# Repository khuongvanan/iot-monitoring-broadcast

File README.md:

# IoT Monitoring & Broadcast

Hệ thống giám sát nhiệt độ, độ ẩm và báo lửa; nhận văn bản hoặc MP3 từ ThingsBoard để phát qua loa. ESP32-S3 xử lý cảm biến, truyền dữ liệu qua modem 4G và điều khiển âm thanh. Cảnh báo lửa được ưu tiên tại thiết bị.

## Sơ đồ hệ thống

```mermaid
flowchart TD
  UI[Dashboard ThingsBoard] <--> TB[ThingsBoard]
  TB <--> MODEM[Modem A7680C]
  MODEM <--> MCU[ESP32-S3]
  SENSOR[SHT31 và cảm biến lửa] --> MCU
  MCU --> DAC[PCM5102A]
  DAC --> AMP[TPA3118D2]
  AMP --> SPK[Loa]
```

## Phần cứng

| Khối | Thành phần | Thư mục |
|---|---|---|
| Điều khiển | ESP32-S3, nguồn và USB | hardware/esp32-controller |
| DAC | PCM5102A | hardware/audio-dac |
| Khuếch đại | TPA3118D2 | hardware/power-amplifier |
| Truyền thông | Modem A7680C qua UART | Module ngoài |
| Cảm biến | SHT31 và cảm biến lửa digital | Kết nối GPIO |

Tên file KiCad bên trong mỗi thư mục được giữ để bảo toàn liên kết project. Thư viện tùy chỉnh rời và model 3D chưa đầy đủ; cần bổ sung trước khi cập nhật linh kiện từ thư viện. Chạy ERC/DRC và tạo Gerber từ PCB trước khi gia công.

## Dùng nhanh

1. Copy `firmware/School_Node/secrets.example.h` thành `secrets.h` cùng thư mục; cấu hình riêng không đưa vào Git.
2. Mở `School_Node.ino` trong Arduino IDE. Cấu hình Arduino-ESP32 3.3.2, ArduinoJson 7.3.2 và flash/PSRAM theo module thực tế.
3. Import `thingsboard/dashboard.json`, chọn lại entity alias và thiết bị điều khiển.
4. Đọc [hướng dẫn sử dụng](docs/usage.md), đặc biệt phần giới hạn TLS, trước khi kết nối dịch vụ.

**Trạng thái TLS:** chỉ có cấu hình TLS cho TTS. HTTPS tới ThingsBoard hiện bị từ chối với mã `-12`; chưa hỗ trợ TLS ThingsBoard hoàn chỉnh. HTTP không bảo vệ token và nội dung trên đường truyền. Không dùng HTTP cho triển khai thực tế có dữ liệu hoặc thông tin xác thực cần bảo vệ.

## Cấu trúc

- `firmware/School_Node`: firmware Arduino và cấu hình mẫu.
- `hardware`: schematic, PCB, project và BOM có sẵn.
- `thingsboard`: một dashboard và mã nguồn widget.
- `tests`: kiểm thử upload, widget và giải mã MP3 trên máy tính.
- `docs/usage.md`: cấu hình, giao thức và xử lý lỗi.

Giới hạn ứng dụng: tối đa 128 KiB văn bản UTF-8, 2 MiB MP3 khi đủ PSRAM; mỗi chunk tối đa 1536 byte. Giới hạn thực tế phụ thuộc bộ nhớ khả dụng.

Xem [kết quả kiểm thử](tests/VALIDATION.md) và [lịch sử thay đổi](CHANGELOG.md). Quyền sử dụng được nêu trong LICENSE; thư viện bên thứ ba có điều khoản riêng trong THIRD_PARTY_NOTICES.txt.

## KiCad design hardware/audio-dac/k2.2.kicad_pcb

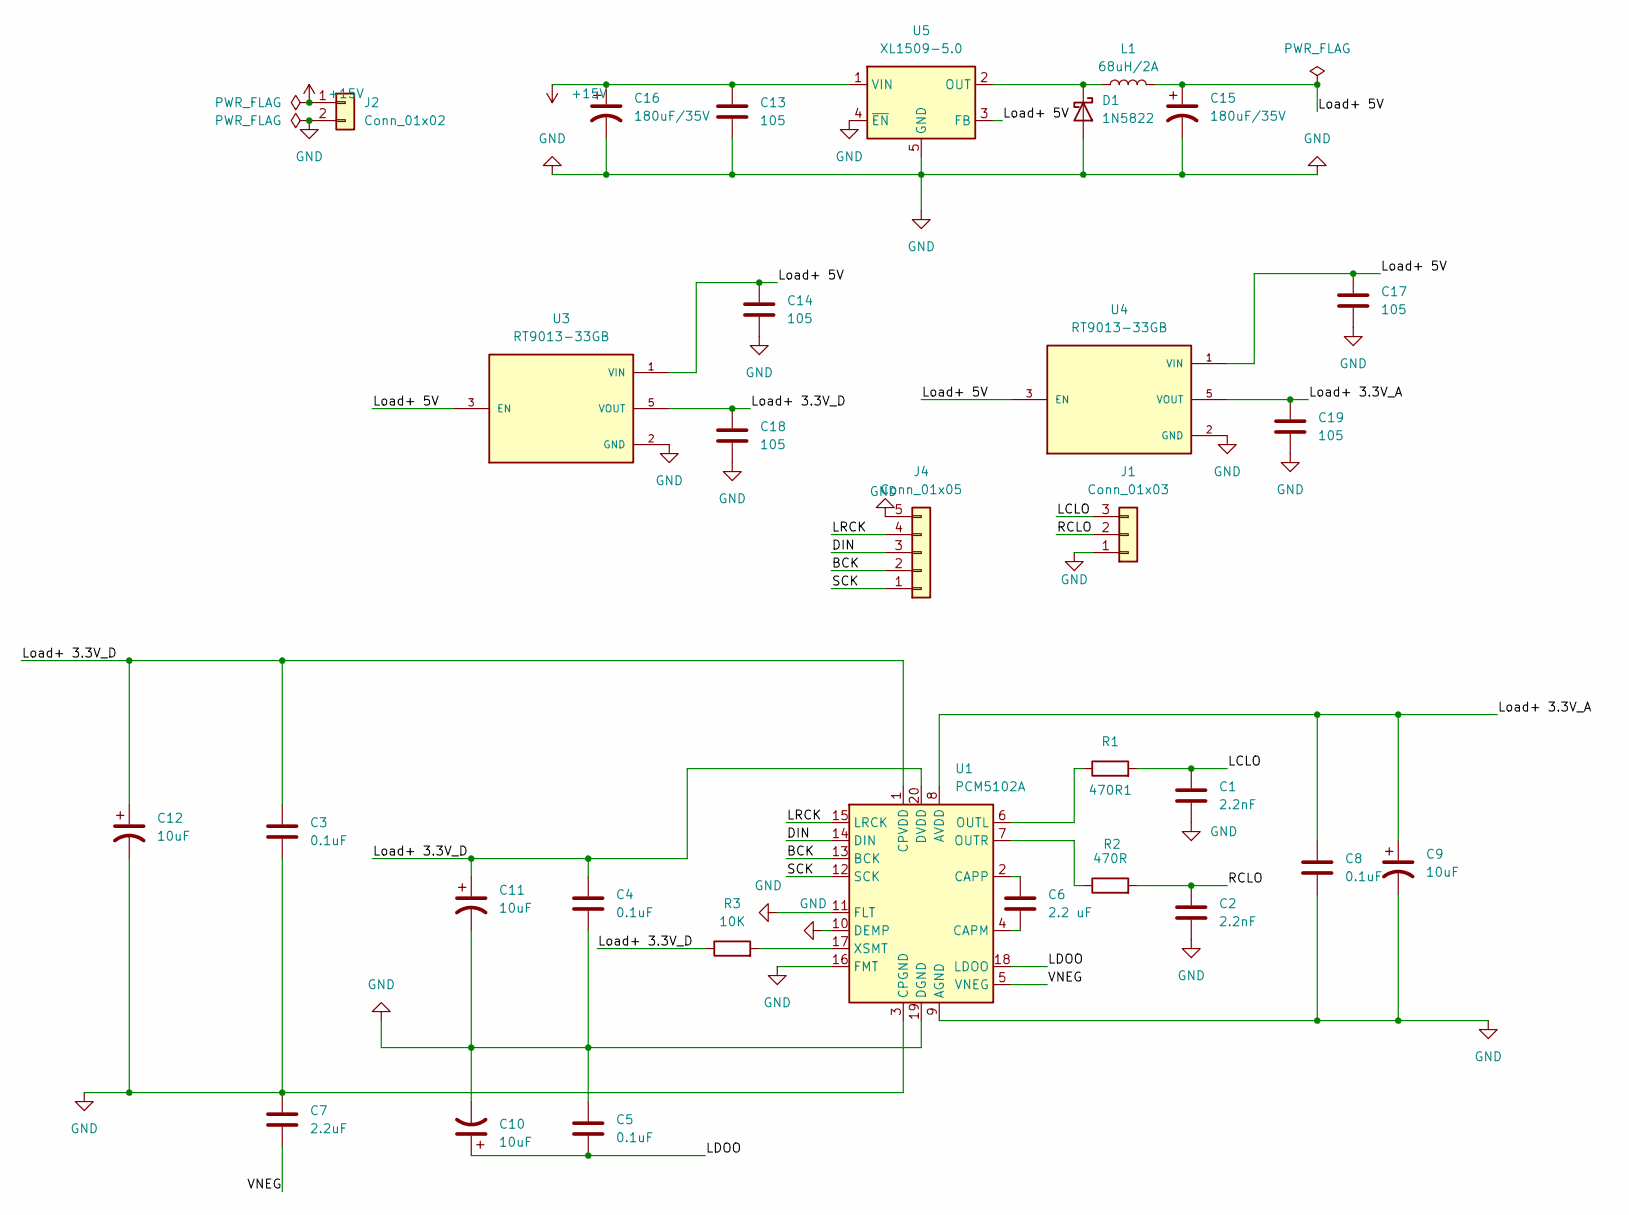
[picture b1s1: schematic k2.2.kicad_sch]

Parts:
470R1: R1; R_0805_2012Metric_Pad1.20x1.40mm_HandSolder
C1, C2: 2.2nF; C_0805_2012Metric_Pad1.18x1.45mm_HandSolder
C3, C4, C5, C8: 0.1uF; C_0805_2012Metric_Pad1.18x1.45mm_HandSolder
C6: 2.2 uF; C_0805_2012Metric_Pad1.18x1.45mm_HandSolder
C7: 2.2uF; C_0805_2012Metric_Pad1.18x1.45mm_HandSolder
C9, C10, C11, C12: 10uF; C_0805_2012Metric_Pad1.18x1.45mm_HandSolder
C13, C14, C17, C18, C19: 105; C_0805_2012Metric_Pad1.18x1.45mm_HandSolder
C15, C16: 180uF/35V; CP_Radial_D6.3mm_P2.50mm
D1: 1N5822; D_SMC_Handsoldering
J1: Conn_01x03; JST_EH_B3B-EH-A_1x03_P2.50mm_Vertical
J2: Conn_01x02; TerminalBlock_Phoenix_MKDS-1,5-2_1x02_P5.00mm_Horizontal
J4: Conn_01x05; JST_EH_B5B-EH-A_1x05_P2.50mm_Vertical
L1: 68uH/2A; L_Taiyo-Yuden_NR-80xx_HandSoldering
R2: 470R; R_0805_2012Metric_Pad1.20x1.40mm_HandSolder
R3: 10K; R_0805_2012Metric_Pad1.20x1.40mm_HandSolder
U1: PCM5102A; TSSOP-20_4.4x6.5mm_P0.65mm
U3, U4: RT9013-33GB; SOT94P279X129-5N; PARTREV Aprill 2011
U5: XL1509-5.0; SOIC-8_3.9x4.9mm_P1.27mm

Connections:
+15V: C13.1, C16.1, J2.1, U5.1 (VIN)
/BCK: J4.2, U1.13 (BCK); also elsewhere on the board
/DIN: J4.3, U1.14 (DIN); also elsewhere on the board
/LCLO: 470R1.2, C1.2, J1.3; also elsewhere on the board
/LDOO: C5.2, C10.1, U1.18 (LDOO)
/LRCK: J4.4, U1.15 (LRCK); also elsewhere on the board
/Load+ 3.3V_A: C8.1, C9.1, C19.1, U1.8 (AVDD), U4.5 (VOUT)
/Load+ 3.3V_D: C3.1, C4.1, C11.1, C12.1, C18.1, R3.1, U1.1 (CPVDD), U1.20 (DVDD), U3.5 (VOUT)
/Load+ 5V: C14.1, C15.1, C17.1, L1.2, U3.1 (VIN), U3.3 (EN), U4.1 (VIN), U4.3 (EN), U5.3 (FB)
/RCLO: C2.2, J1.2, R2.2
/SCK: J4.1, U1.12 (SCK); also elsewhere on the board
/VNEG: C7.1, U1.5 (VNEG)
GND: C1.1, C2.1, C3.2, C4.2, C5.1, C7.2, C8.2, C9.2, C10.2, C11.2, C12.2, C13.2, C14.2, C15.2, C16.2, C17.2, C18.2, C19.2, D1.2 (A), J1.1, J2.2, J4.5, U1.3 (CPGND), U1.9 (AGND), U1.10 (DEMP), U1.11 (FLT), U1.16 (FMT), U1.19 (DGND), U3.2 (GND), U4.2 (GND), U5.4 (~EN), U5.5 (GND), U5.6 (GND), U5.7 (GND), U5.8 (GND); also elsewhere on the board
unnamed: D1.1 (K), L1.1, U5.2 (OUT)
unnamed: C6.2, U1.4 (CAPM)
unnamed: C6.1, U1.2 (CAPP)
unnamed 16: 470R1.1, U1.6 (OUTL); also elsewhere on the board
unnamed: R2.1, U1.7 (OUTR)
unnamed: R3.2, U1.17 (XSMT)

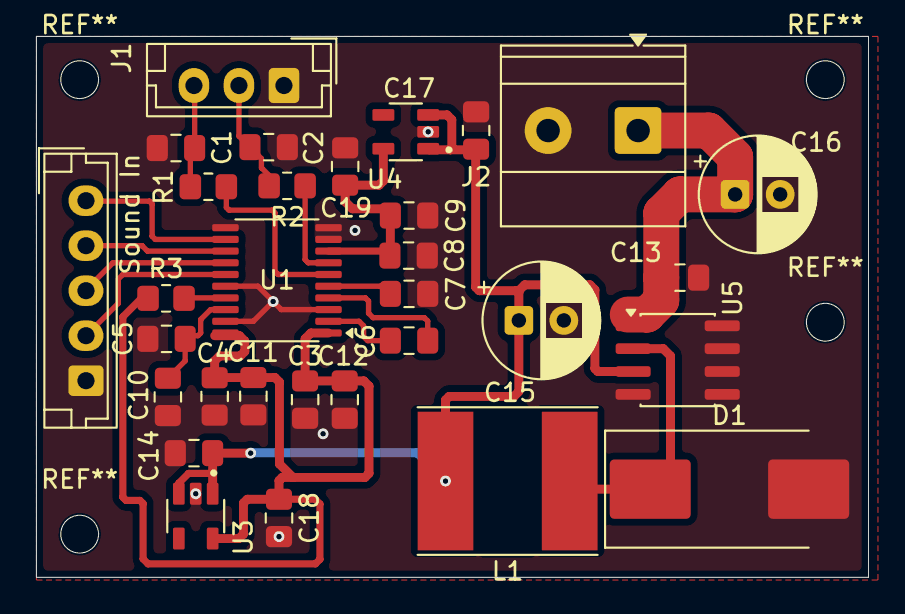
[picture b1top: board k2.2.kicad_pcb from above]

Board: 2 copper layers, 46.2 x 30.0 mm, 31 parts (0 on the bottom side), 19 nets.

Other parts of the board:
R1: R1; R_0805_2012Metric_Pad1.20x1.40mm_HandSolder
Sound In: Conn_01x05; JST_EH_B5B-EH-A_1x05_P2.50mm_Vertical

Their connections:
/BCK: Sound In.2; also elsewhere on the board
/DIN: Sound In.3; also elsewhere on the board
/LCLO: R1.2; also elsewhere on the board
/LRCK: Sound In.4; also elsewhere on the board
/SCK: Sound In.1; also elsewhere on the board
GND: Sound In.5; also elsewhere on the board
unnamed 16: R1.1; also elsewhere on the board

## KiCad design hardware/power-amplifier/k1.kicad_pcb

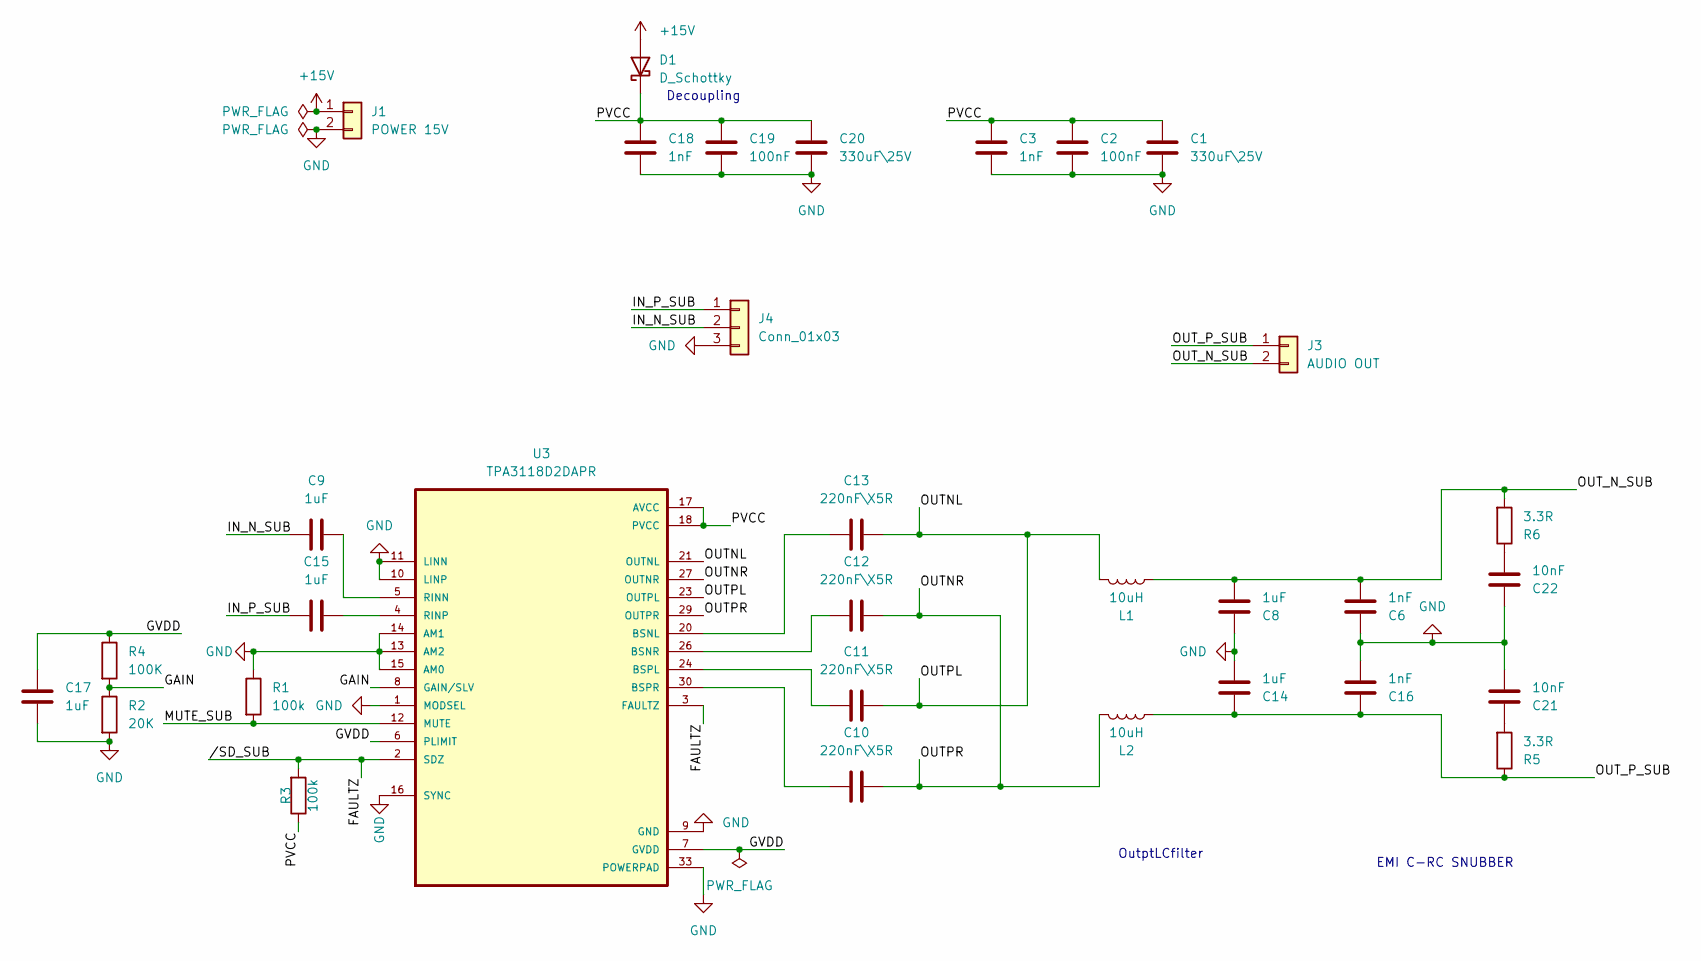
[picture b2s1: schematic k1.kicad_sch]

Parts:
C1, C20: 330uF\25V; CP_Radial_D8.0mm_P3.50mm
C2, C19: 100nF; C_0805_2012Metric_Pad1.18x1.45mm_HandSolder
C3, C6, C16, C18: 1nF; C_0805_2012Metric_Pad1.18x1.45mm_HandSolder
C8, C14: 1uF; C_1206_3216Metric_Pad1.33x1.80mm_HandSolder
C9, C15, C17: 1uF; C_0805_2012Metric_Pad1.18x1.45mm_HandSolder
C10, C11, C12, C13: 220nF\X5R; C_0805_2012Metric_Pad1.18x1.45mm_HandSolder
C21, C22: 10nF; C_0805_2012Metric_Pad1.18x1.45mm_HandSolder
D1: D_Schottky
J1: POWER 15V; TerminalBlock_Phoenix_MKDS-1,5-2_1x02_P5.00mm_Horizontal
J3: AUDIO OUT; TerminalBlock_Phoenix_MKDS-1,5-2_1x02_P5.00mm_Horizontal
J4: Conn_01x03; JST_EH_B3B-EH-A_1x03_P2.50mm_Vertical
L1, L2: 10uH; L_Taiyo-Yuden_NR-10050_9.8x10.0mm_HandSoldering
R1, R3: 100k; R_0805_2012Metric_Pad1.20x1.40mm_HandSolder
R2: 20K; R_0805_2012Metric_Pad1.20x1.40mm_HandSolder
R4: 100K; R_0805_2012Metric_Pad1.20x1.40mm_HandSolder
R5, R6: 3.3R; R_0805_2012Metric_Pad1.20x1.40mm_HandSolder
U3: TPA3118D2DAPR; SOP65P810X120-33N; DigiKey_Part_Number 296-38572-1-ND

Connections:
+15V: D1.2 (A), J1.1
/FAULTZ: R3.2, U3.2 (SDZ), U3.3 (FAULTZ)
/GAIN: R2.1, R4.2, U3.8 (GAIN/SLV)
/GVDD: C17.2, R4.1, U3.6 (PLIMIT), U3.7 (GVDD)
/IN_N_SUB: C9.1, J4.2
/IN_P_SUB: C15.1, J4.1
/MUTE_SUB: R1.2, U3.12 (MUTE)
/OUTNL: C11.2, C13.2, L1.1, U3.21 (OUTNL), U3.23 (OUTPL)
/OUTNR: C10.2, C12.2, L2.1, U3.27 (OUTNR), U3.29 (OUTPR)
/OUT_N_SUB: C6.2, C8.2, J3.2, L1.2, R6.2
/OUT_P_SUB: C14.1, C16.1, J3.1, L2.2, R5.1
GND: C1.2, C2.2, C3.2, C6.1, C8.1, C14.2, C16.2, C17.1, C18.2, C19.2, C20.2, C21.2, C22.1, J1.2, J4.3, R1.1, R2.2, U3.1 (MODSEL), U3.9 (GND), U3.10 (LINP), U3.11 (LINN), U3.13 (AM2), U3.14 (AM1), U3.15 (AM0), U3.16 (SYNC), U3.22 (GND), U3.25 (GND), U3.28 (GND), U3.33 (POWERPAD)
unnamed: C21.1, R5.2
unnamed: C22.2, R6.1
unnamed: C13.1, U3.20 (BSNL)
unnamed: C12.1, U3.26 (BSNR)
unnamed: C11.1, U3.24 (BSPL)
unnamed: C10.1, U3.30 (BSPR)
unnamed: C9.2, U3.5 (RINN)
unnamed: C15.2, U3.4 (RINP)
PVCC: C1.1, C2.1, C3.1, C18.1, C19.1, C20.1, D1.1 (K), R3.1, U3.17 (AVCC), U3.18 (PVCC), U3.19 (PVCC), U3.31 (PVCC), U3.32 (PVCC)

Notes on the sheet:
OutptLCfilter
Decoupling
EMI C-RC SNUBBER

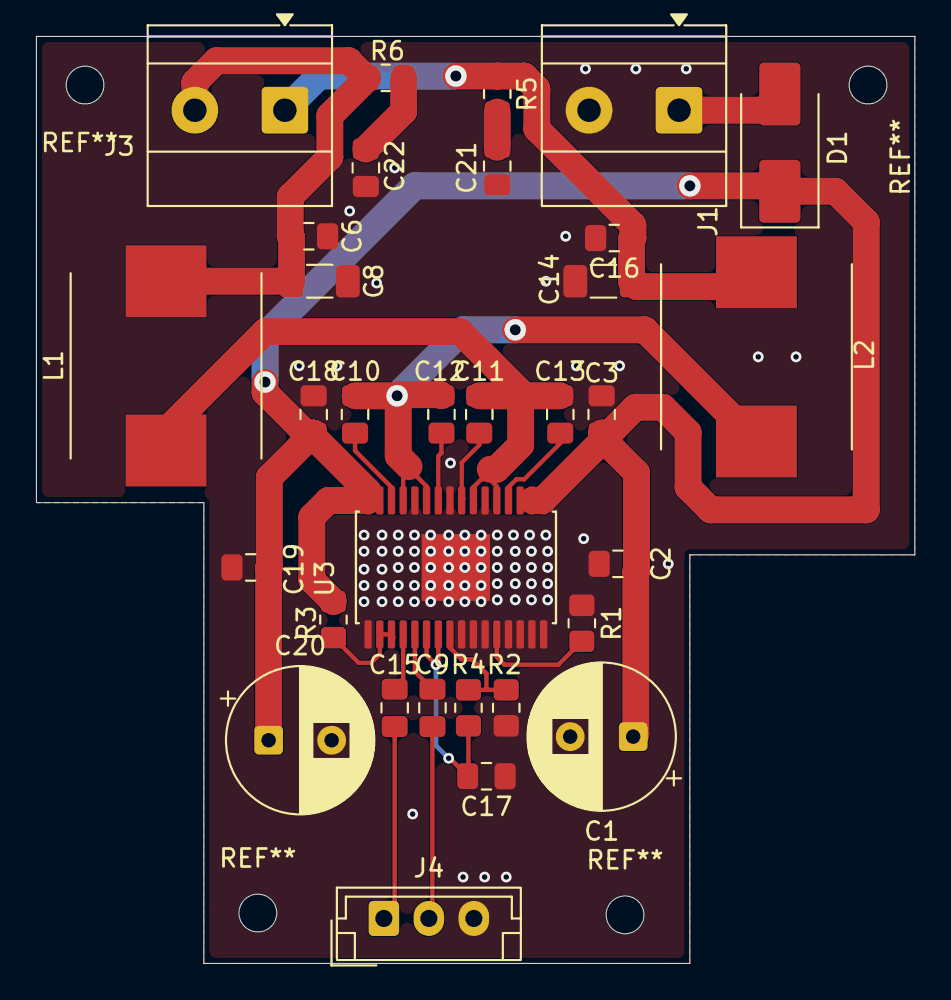
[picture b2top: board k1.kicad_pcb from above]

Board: 2 copper layers, 48.8 x 51.5 mm, 32 parts (0 on the bottom side), 21 nets.

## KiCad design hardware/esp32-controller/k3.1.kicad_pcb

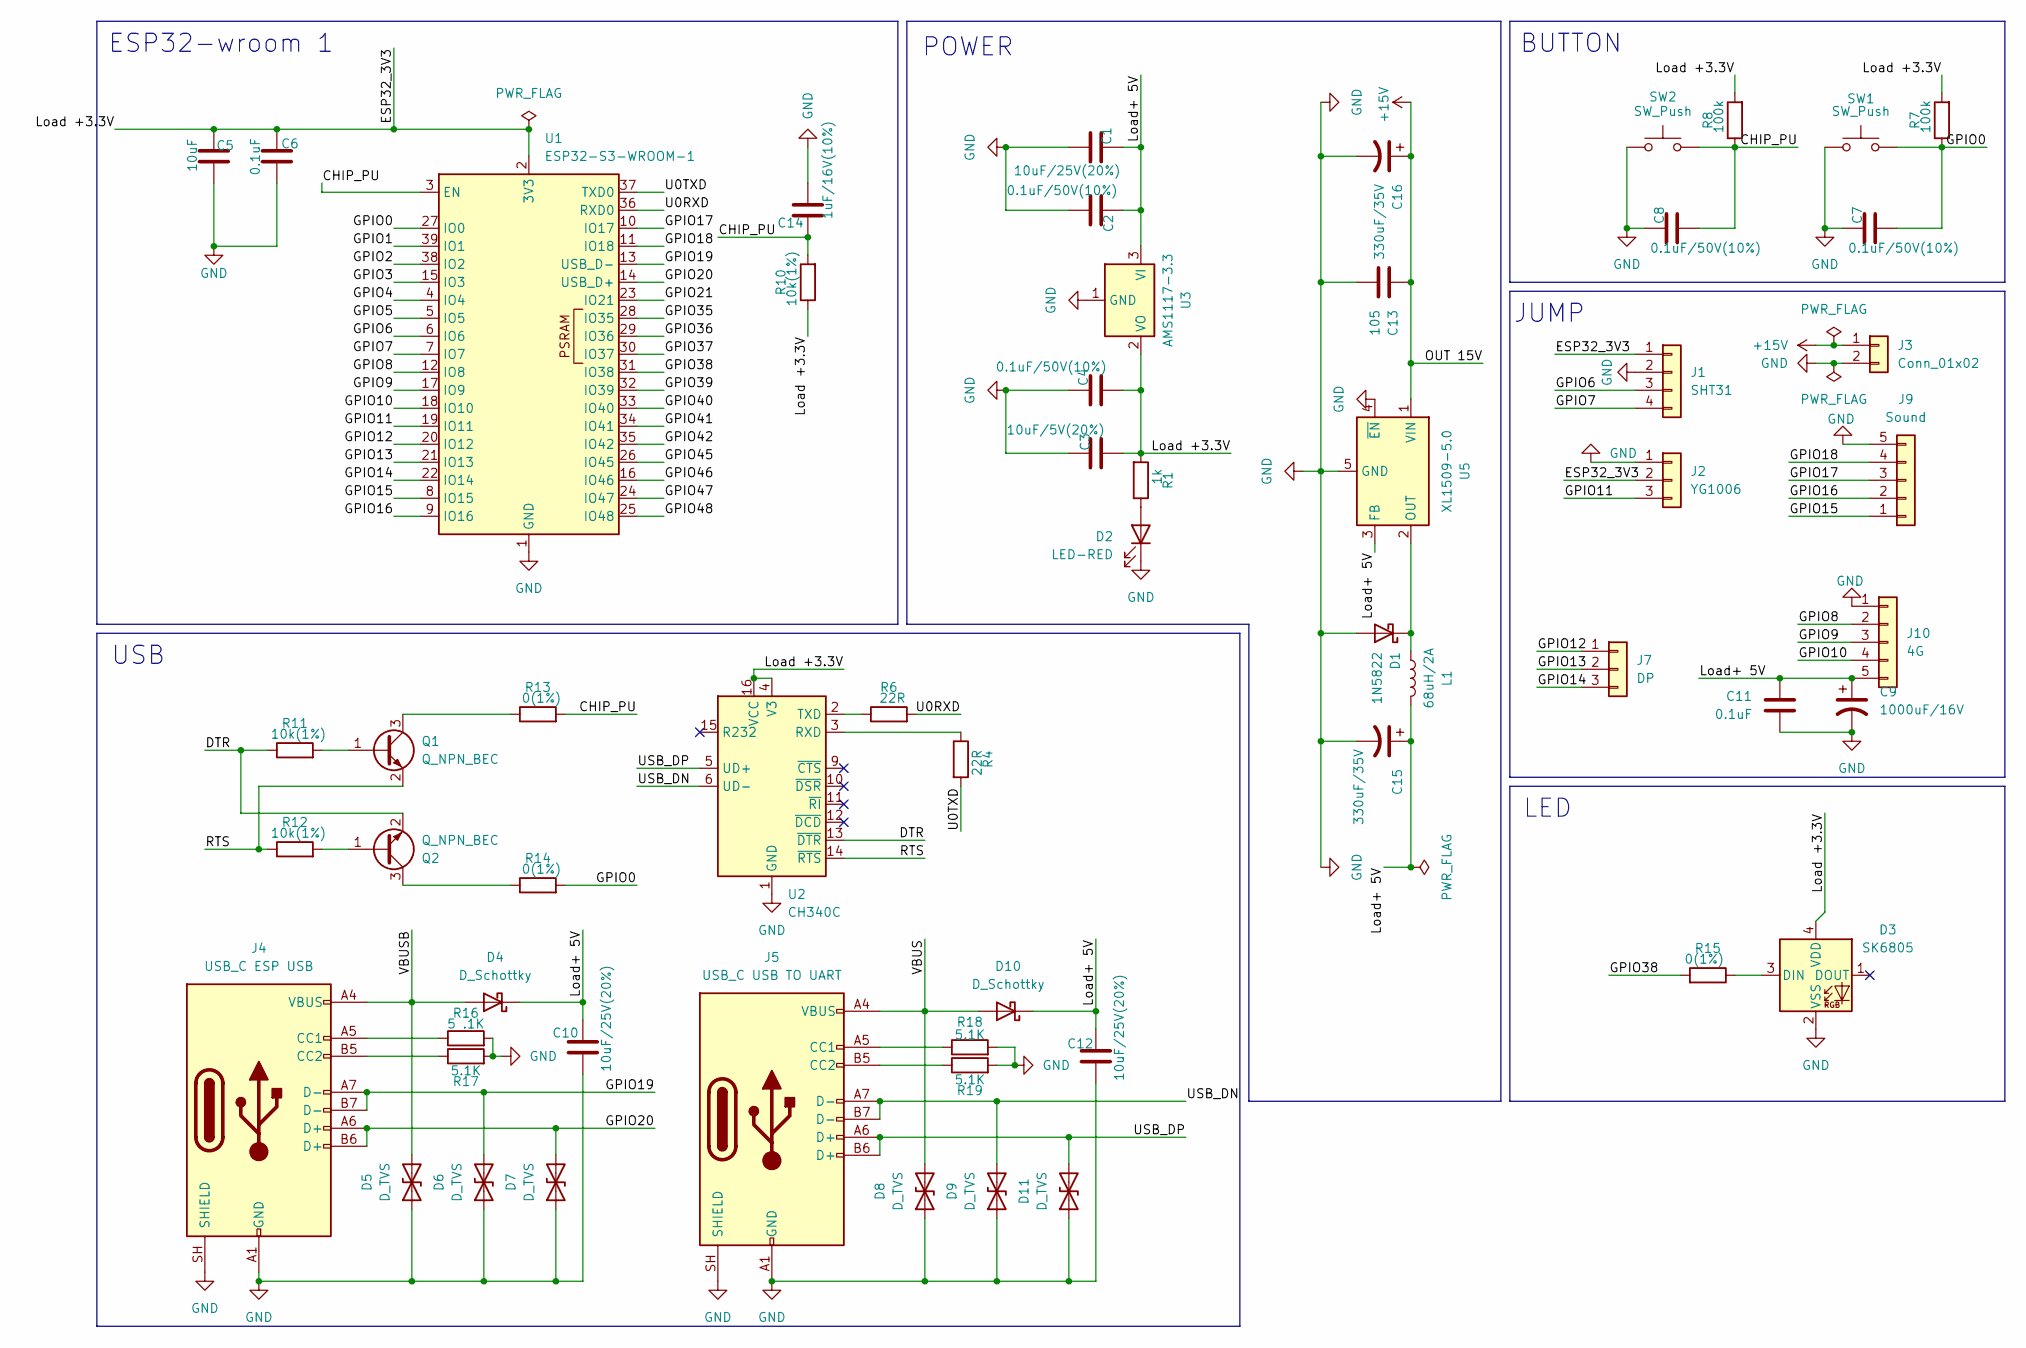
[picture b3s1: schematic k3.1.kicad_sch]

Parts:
C1, C10, C12: 10uF/25V(20%); C_1206_3216Metric_Pad1.33x1.80mm_HandSolder
C2, C4, C7, C8: 0.1uF/50V(10%); C_0805_2012Metric_Pad1.18x1.45mm_HandSolder
C3: 10uF/5V(20%); C_0805_2012Metric_Pad1.18x1.45mm_HandSolder
C5: 10uF; C_0805_2012Metric_Pad1.18x1.45mm_HandSolder
C6, C11: 0.1uF; C_0805_2012Metric_Pad1.18x1.45mm_HandSolder
C9: 1000uF/16V; CP_Radial_D8.0mm_P3.50mm
C13: 105; C_0805_2012Metric_Pad1.18x1.45mm_HandSolder
C14: 1uF/16V(10%); C_0805_2012Metric_Pad1.18x1.45mm_HandSolder
C15, C16: 330uF/35V; CP_Radial_D8.0mm_P5.00mm
D1: 1N5822; D_SMC_Handsoldering
D2: LED-RED; LED_0805_2012Metric_Pad1.15x1.40mm_HandSolder
D3: SK6805; LED_SK6805_PLCC4_2.4x2.7mm_P1.3mm
D4, D10: D_Schottky; D_SMA_Handsoldering
D5, D6, D7, D8, D9, D11: D_TVS; D_1206_3216Metric_Pad1.42x1.75mm_HandSolder
J1: SHT31; JST_EH_B4B-EH-A_1x04_P2.50mm_Vertical
J2: YG1006; JST_EH_B3B-EH-A_1x03_P2.50mm_Vertical
J3: Conn_01x02; TerminalBlock_Phoenix_MKDS-1,5-2-5.08_1x02_P5.08mm_Horizont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
J4: USB_C ESP USB; USB_C_Receptacle_HCTL_HC-TYPE-C-16P-01A
J5: USB_C USB TO UART; USB_C_Receptacle_HCTL_HC-TYPE-C-16P-01A
J7: DP; JST_EH_B3B-EH-A_1x03_P2.50mm_Vertical
J9: Sound; JST_EH_B5B-EH-A_1x05_P2.50mm_Vertical
J10: 4G; JST_EH_B5B-EH-A_1x05_P2.50mm_Vertical
L1: 68uH/2A; L_Taiyo-Yuden_NR-80xx_HandSoldering
Q1, Q2: Q_NPN_BEC; SOT-23
R1: 1k; R_0805_2012Metric_Pad1.20x1.40mm_HandSolder
R4, R6: 22R; R_0805_2012Metric_Pad1.20x1.40mm_HandSolder
R7, R8: 100k; R_0805_2012Metric_Pad1.20x1.40mm_HandSolder
R10, R11, R12: 10k(1%); R_0805_2012Metric_Pad1.20x1.40mm_HandSolder
R13, R14, R15: 0(1%); R_0805_2012Metric_Pad1.20x1.40mm_HandSolder
R16: 5 .1K; R_0805_2012Metric_Pad1.20x1.40mm_HandSolder
R17, R18, R19: 5.1K; R_0805_2012Metric_Pad1.20x1.40mm_HandSolder
SW1, SW2: SW_Push; SW_SPST_FSMSM
U1: ESP32-S3-WROOM-1
U2: CH340C; SOIC-16_3.9x9.9mm_P1.27mm
U3: AMS1117-3.3; SOT-223-3_TabPin2
U5: XL1509-5.0; SOIC-8_3.9x4.9mm_P1.27mm

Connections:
+15V: C13.1, C16.1, J3.1, U5.1 (VIN)
/CHIP_PU: C8.2, C14.1, R8.1, R10.2, R13.2, SW2.2, U1.3 (EN)
/DTR: Q2.2 (E), R11.1, U2.13 (~DTR)
/ESP32_3V3: C3.2, C4.2, C5.1, C6.1, D3.4 (VDD), J1.1, J2.2, R1.2, R7.2, R8.2, R10.1, U1.2 (3V3), U2.4 (V3), U2.16 (VCC), U3.2 (VO)
/GPIO0: C7.2, R7.1, R14.2, SW1.2, U1.27 (IO0)
/GPIO1: U1.39 (IO1)
/GPIO2: U1.38 (IO2)
/GPIO3: U1.15 (IO3)
/GPIO4: U1.4 (IO4)
/GPIO5: U1.5 (IO5)
/GPIO6: J1.3, U1.6 (IO6)
/GPIO7: J1.4, U1.7 (IO7)
/GPIO8: J10.2, U1.12 (IO8); also elsewhere on the board
/GPIO9: J10.3, U1.17 (IO9); also elsewhere on the board
/GPIO10: J10.4, U1.18 (IO10); also elsewhere on the board
/GPIO11: J2.3, U1.19 (IO11)
/GPIO12: J7.1, U1.20 (IO12)
/GPIO13: J7.2, U1.21 (IO13)
/GPIO14: J7.3, U1.22 (IO14)
/GPIO15: J9.1, U1.8 (IO15)
/GPIO16: J9.2, U1.9 (IO16)
/GPIO17: J9.3, U1.10 (IO17)
/GPIO18: J9.4, U1.11 (IO18)
/GPIO19: D6.2 (A2), J4.A7 (D-), J4.B7 (D-), U1.13 (USB_D-)
/GPIO20: D7.2 (A2), J4.A6 (D+), J4.B6 (D+), U1.14 (USB_D+)
/GPIO21: U1.23 (IO21)
/GPIO35: U1.28 (IO35)
/GPIO36: U1.29 (IO36)
/GPIO37: U1.30 (IO37)
/GPIO38: R15.2, U1.31 (IO38)
/GPIO39: U1.32 (IO39)
/GPIO40: U1.33 (IO40)
/GPIO41: U1.34 (IO41)
/GPIO42: U1.35 (IO42)
/GPIO45: U1.26 (IO45)
/GPIO46: U1.16 (IO46)
/GPIO47: U1.24 (IO47)
/GPIO48: U1.25 (IO48)
/Load+ 5V: C1.1, C2.1, C9.1, C10.2, C11.1, C12.2, C15.1, D4.1 (K), D10.1 (K), J10.5, L1.2, U3.3 (VI), U5.3 (FB); also elsewhere on the board
/RTS: Q1.2 (E), R12.1, U2.14 (~RTS)
/U0RXD: R6.2, U1.36 (RXD0)
/U0TXD: R4.2, U1.37 (TXD0)
/USB_DN: D9.2 (A2), J5.A7 (D-), J5.B7 (D-), U2.6 (UD-)
/USB_DP: D11.2 (A2), J5.A6 (D+), J5.B6 (D+), U2.5 (UD+)
/VBUS: D8.2 (A2), D10.2 (A), J5.A4 (VBUS), J5.A9 (VBUS), J5.B4 (VBUS), J5.B9 (VBUS)
/VBUSB: D4.2 (A), D5.2 (A2), J4.A4 (VBUS), J4.A9 (VBUS), J4.B4 (VBUS), J4.B9 (VBUS)
GND: C1.2, C2.2, C3.1, C4.1, C5.2, C6.2, C7.1, C8.1, C9.2, C10.1, C11.2, C12.1, C13.2, C14.2, C15.2, C16.2, D1.2 (A), D2.1 (K), D3.2 (VSS), D5.1 (A1), D6.1 (A1), D7.1 (A1), D8.1 (A1), D9.1 (A1), D11.1 (A1), J1.2, J2.1, J3.2, J4.A1 (GND), J4.A12 (GND), J4.B1 (GND), J4.B12 (GND), J4.SH (SHIELD), J5.A1 (GND), J5.A12 (GND), J5.B1 (GND), J5.B12 (GND), J5.SH (SHIELD), J9.5, J10.1, R16.2, R17.2, R18.2, R19.2, SW1.1, SW2.1, U1.1 (GND), U1.40 (GND), U1.41 (GND), U2.1 (GND), U3.1 (GND), U5.4 (~EN), U5.5 (GND), U5.6 (GND), U5.7 (GND), U5.8 (GND); also elsewhere on the board
unnamed: D1.1 (K), L1.1, U5.2 (OUT)
unnamed: D2.2 (A), R1.1
unnamed: D3.3 (DIN), R15.1
unnamed: J4.A5 (CC1), R16.1
unnamed: J4.B5 (CC2), R17.1
unnamed: J5.A5 (CC1), R18.1
unnamed: J5.B5 (CC2), R19.1
unnamed: Q1.1 (B), R11.2
unnamed: Q1.3 (C), R13.1
unnamed: Q2.1 (B), R12.2
unnamed: Q2.3 (C), R14.1
unnamed: R4.1, U2.3 (RXD)
unnamed: R6.1, U2.2 (TXD)

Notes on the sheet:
POWER
BUTTON
JUMP
ESP32-wroom 1
LED
USB

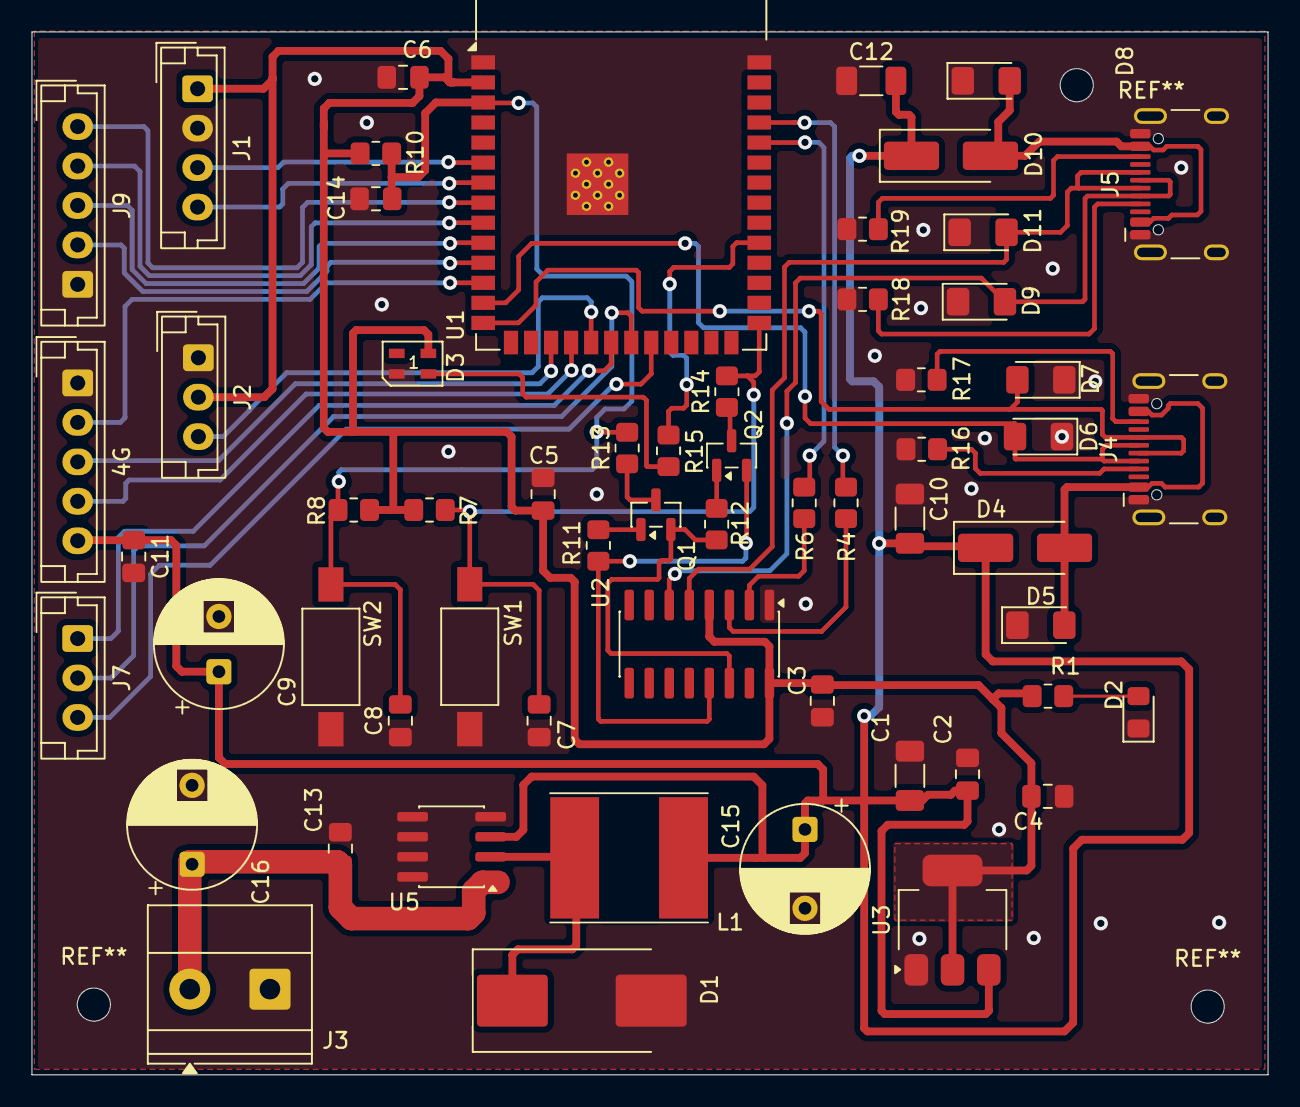
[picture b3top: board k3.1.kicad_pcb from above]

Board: 2 copper layers, 78.3 x 66.1 mm, 59 parts (0 on the bottom side), 43 nets.

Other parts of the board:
4G: 4G; JST_EH_B5B-EH-A_1x05_P2.50mm_Vertical

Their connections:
/GPIO8: 4G.2; also elsewhere on the board
/GPIO9: 4G.3; also elsewhere on the board
/GPIO10: 4G.4; also elsewhere on the board
/Load+ 5V: 4G.5; also elsewhere on the board
GND: 4G.1; also elsewhere on the board
